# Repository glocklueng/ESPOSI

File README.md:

# ESPOSI
A family of ESP8266 wifi-enabled sensor, controller, and programmer boards.

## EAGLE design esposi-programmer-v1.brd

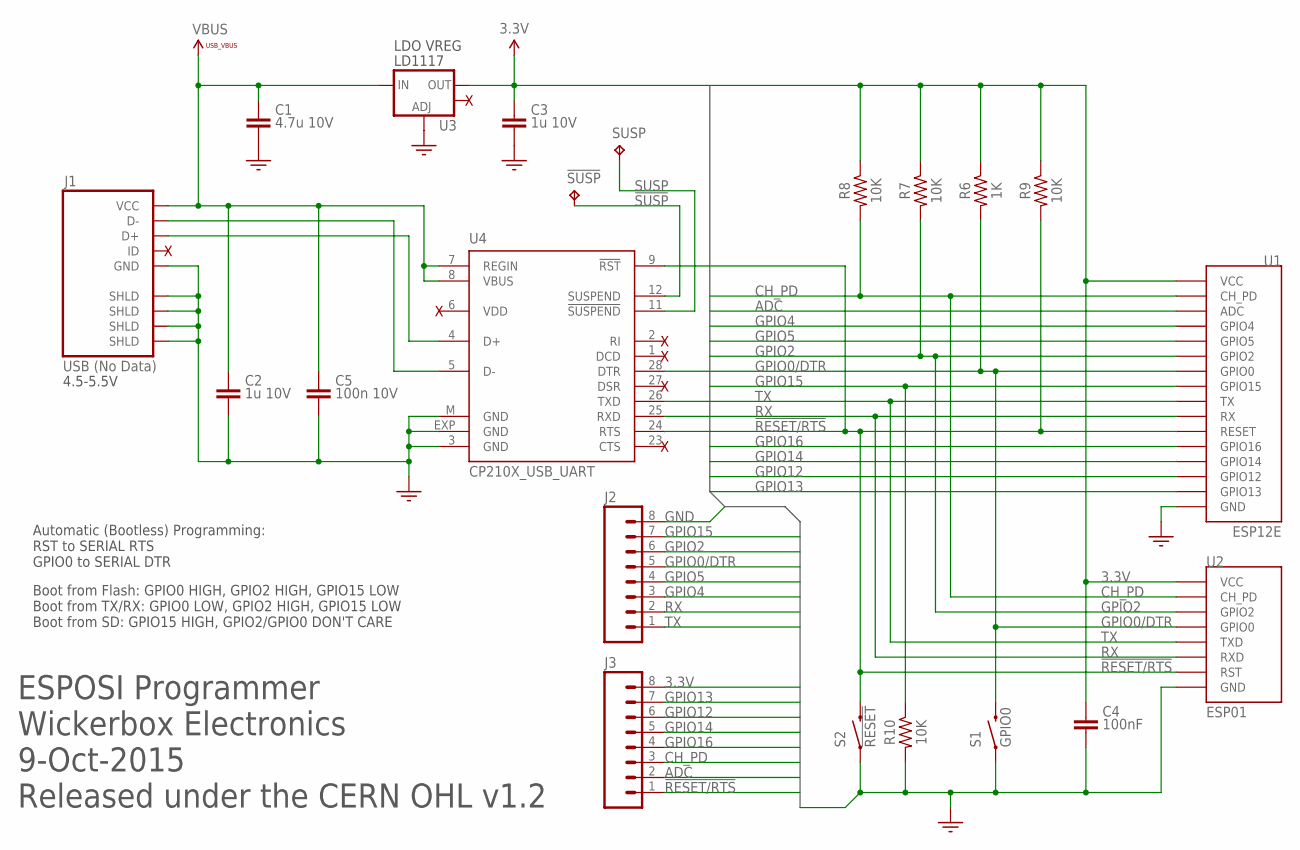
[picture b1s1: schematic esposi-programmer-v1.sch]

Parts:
!SUSP: TESTPAD_TPB1,27; TESTPAD_B1,27
C1: 4.7u 10V; RLC-0805
C2, C3: 1u 10V; RLC-0603
C4: 100nF; RLC-0402
C5: 100n 10V; RLC-0402
J1: USB (No Data); ZX62D-B-5P8
J2, J3: M08NO_SILK_FEMALE_PTH; 1X08_NO_SILK
R6: 1K; RLC-0402
R7, R8, R9, R10: 10K; RLC-0402
S1: GPIO0; TACTILE-SWITCH-1101NE
S2: !RESET; TACTILE-SWITCH-1101NE
SUSP: TESTPAD_TPB1,27; TESTPAD_B1,27
U1: ESP12E; ESP12
U2: ESP01
U3: V_REG_LM1117SOT223; SOT223
U4: CP210X_USB_UART; MLP28

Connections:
3.3V: C3.2 (1), C4.1, J3.8, R6.1, R7.1, R8.1, R9.1, U1.VCC, U2.VCC, U3.2 (OUT)
!RESET/RTS: J3.1, R9.2, S2.2, U1.RESET, U2.RST, U4.9 (!RST), U4.24 (RTS)
!SUSP: !SUSP.TP, U4.12 (SUSPEND)
ADC: J3.2, U1.ADC
CH_PD: J3.3, R8.2, U1.CH_PD, U2.CH_PD
D+: J1.P3 (D+), U4.4 (D+)
D-: J1.P2 (D-), U4.5 (D-)
GND: C1.2, C2.1 (2), C3.1 (2), C4.2, C5.2, J1.P5 (GND), J1.P$1 (SHLD), J1.P$2 (SHLD), J1.P$3 (SHLD), J1.P$4 (SHLD), J2.8, R10.2, S1.1, S2.1, U1.GND, U2.GND, U3.1 (ADJ), U4.3 (GND), U4.EXP (GND), U4.M (GND)
GPIO0/DTR: J2.5, R6.2, S1.2, U1.GPIO0, U2.GPIO0, U4.28 (DTR)
GPIO2: J2.6, R7.2, U1.GPIO2, U2.GPIO2
GPIO4: J2.3, U1.GPIO4
GPIO5: J2.4, U1.GPIO5
GPIO12: J3.6, U1.GPIO12
GPIO13: J3.7, U1.GPIO13
GPIO14: J3.5, U1.GPIO14
GPIO15: J2.7, R10.1, U1.GPIO15
GPIO16: J3.4, U1.GPIO16
RX: J2.2, U1.RX, U2.RX (RXD), U4.25 (RXD)
SUSP: SUSP.TP, U4.11 (!SUSPEND)
TX: J2.1, U1.TX, U2.TX (TXD), U4.26 (TXD)
VBUS: C1.1, C2.2 (1), C5.1, J1.P1 (VCC), U3.3 (IN), U4.7 (REGIN), U4.8 (VBUS)
VDD: U4.6 (VDD)

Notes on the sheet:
LD1117
4.5-5.5V
ESPOSI Programmer Wickerbox Electronics 9-Oct-2015 Released under the CERN OHL v1.2
Boot from Flash: GPIO0 HIGH, GPIO2 HIGH, GPIO15 LOW Boot from TX/RX: GPIO0 LOW, GPIO2 HIGH, GPIO15 LOW Boot from SD: GPIO15 HIGH, GPIO2/GPIO0 DON'T CARE
Automatic (Bootless) Programming: RST to SERIAL RTS GPIO0 to SERIAL DTR
LDO VREG

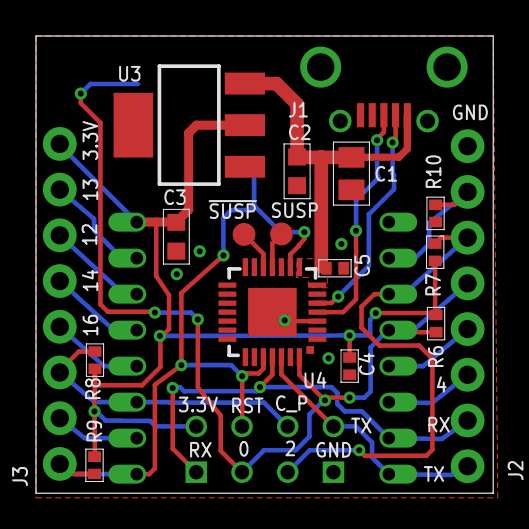
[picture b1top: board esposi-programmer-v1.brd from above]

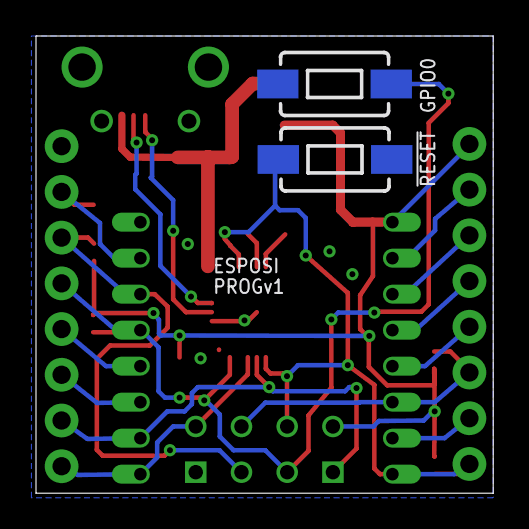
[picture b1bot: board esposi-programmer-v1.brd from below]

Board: 2 copper layers, 25.4 x 25.4 mm, 21 parts (3 on the bottom side), 21 nets.

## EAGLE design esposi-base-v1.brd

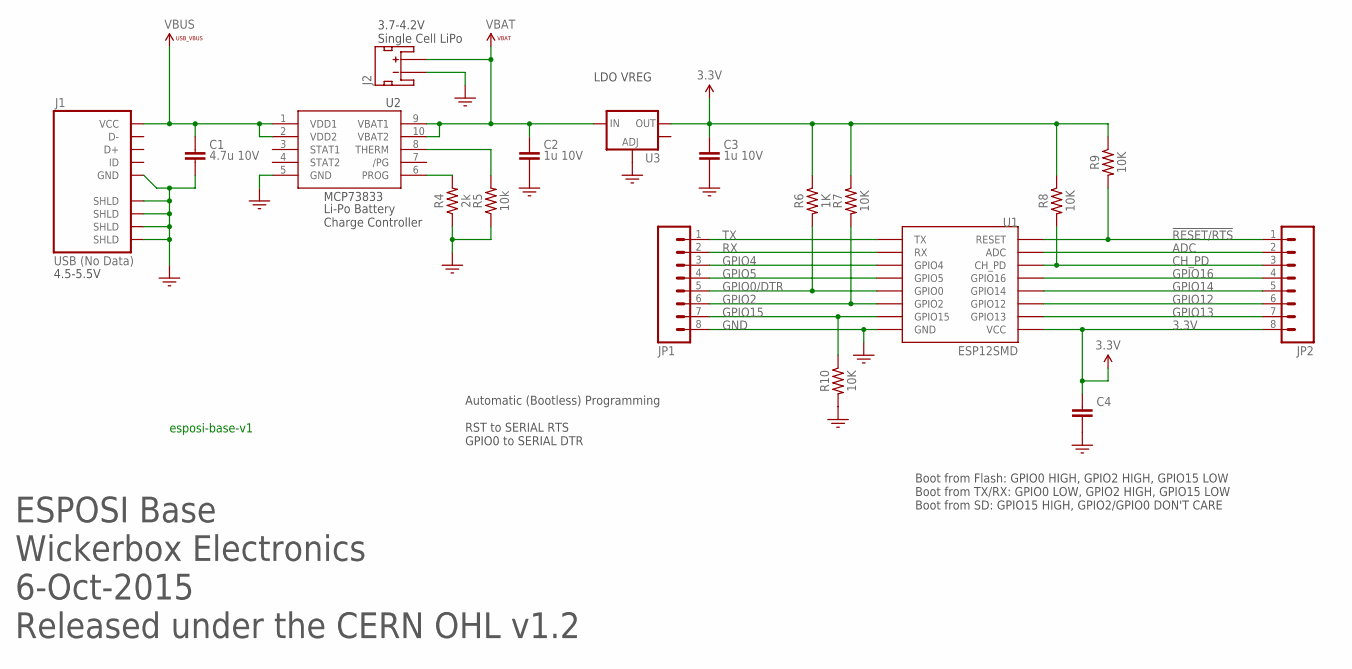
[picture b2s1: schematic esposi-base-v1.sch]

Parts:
C1: 4.7u 10V; RLC-0805
C2, C3: 1u 10V; RLC-0603
C4: CAP-0402; RLC-0402
J1: USB (No Data); ZX62D-B-5P8
J2: JST_2MM_MALE; JST-2-SMD
JP1, JP2: M08NO_SILK_FEMALE_PTH; 1X08_NO_SILK
R4: 2k; RLC-0402
R5: 10k; RLC-0402
R6: 1K; RLC-0402
R7, R8, R9, R10: 10K; RLC-0402
U1: ESP12SMD; ESP12_SMD
U2: MCP73833-UN; MSOP10
U3: V_REG_LM1117SOT223; SOT223

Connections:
3.3V: C3.2 (1), C4.1, JP2.8, R6.1, R7.1, R8.1, R9.1, U1.VCC, U3.2 (OUT)
!RESET/RTS: JP2.1, R9.2, U1.RESET
ADC: JP2.2, U1.ADC
CH_PD: JP2.3, R8.2, U1.CH_PD
GND: C1.2, C2.1 (2), C3.1 (2), C4.2, J1.P5 (GND), J1.P$1 (SHLD), J1.P$2 (SHLD), J1.P$3 (SHLD), J1.P$4 (SHLD), J2.1 (-), JP1.8, R4.1, R5.1, R10.2, U1.GND, U2.5 (GND), U3.1 (ADJ)
GPIO0/DTR: JP1.5, R6.2, U1.GPIO0
GPIO2: JP1.6, R7.2, U1.GPIO2
GPIO4: JP1.3, U1.GPIO4
GPIO5: JP1.4, U1.GPIO5
GPIO12: JP2.6, U1.GPIO12
GPIO13: JP2.7, U1.GPIO13
GPIO14: JP2.5, U1.GPIO14
GPIO15: JP1.7, R10.1, U1.GPIO15
GPIO16: JP2.4, U1.GPIO16
PROG: R4.2, U2.6 (PROG)
RX: JP1.2, U1.RX
THERM: R5.2, U2.8 (THERM)
TX: JP1.1, U1.TX
VBAT: C2.2 (1), J2.2 (+), U2.9 (VBAT1), U2.10 (VBAT2), U3.3 (IN)
VBUS: C1.1, J1.P1 (VCC), U2.1 (VDD1), U2.2 (VDD2)

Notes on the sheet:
LDO VREG
4.5-5.5V
Li-Po Battery Charge Controller
3.7-4.2V Single Cell LiPo
ESPOSI Base Wickerbox Electronics 6-Oct-2015 Released under the CERN OHL v1.2
Boot from Flash: GPIO0 HIGH, GPIO2 HIGH, GPIO15 LOW Boot from TX/RX: GPIO0 LOW, GPIO2 HIGH, GPIO15 LOW Boot from SD: GPIO15 HIGH, GPIO2/GPIO0 DON'T CARE
Automatic (Bootless) Programming RST to SERIAL RTS GPIO0 to SERIAL DTR

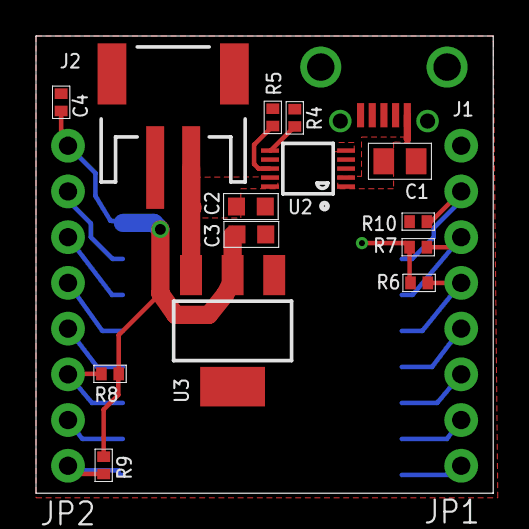
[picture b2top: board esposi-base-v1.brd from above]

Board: 2 copper layers, 25.4 x 25.4 mm, 18 parts (1 on the bottom side), 20 nets.

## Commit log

2015-10-15 Added v1 of the base unit.
2015-10-15 Added v1 of the programmer unit.

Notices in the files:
parts and their libraries:
SparkFun-Connectors: Licensing: Creative Commons ShareAlike 4.0 International - https://creativecommons.org/licenses/by-sa/4.0
PatternAgents-Beautify: License : http://creativecommons.org/licenses/by-sa/3.0
(Creative Commons 3.0)
